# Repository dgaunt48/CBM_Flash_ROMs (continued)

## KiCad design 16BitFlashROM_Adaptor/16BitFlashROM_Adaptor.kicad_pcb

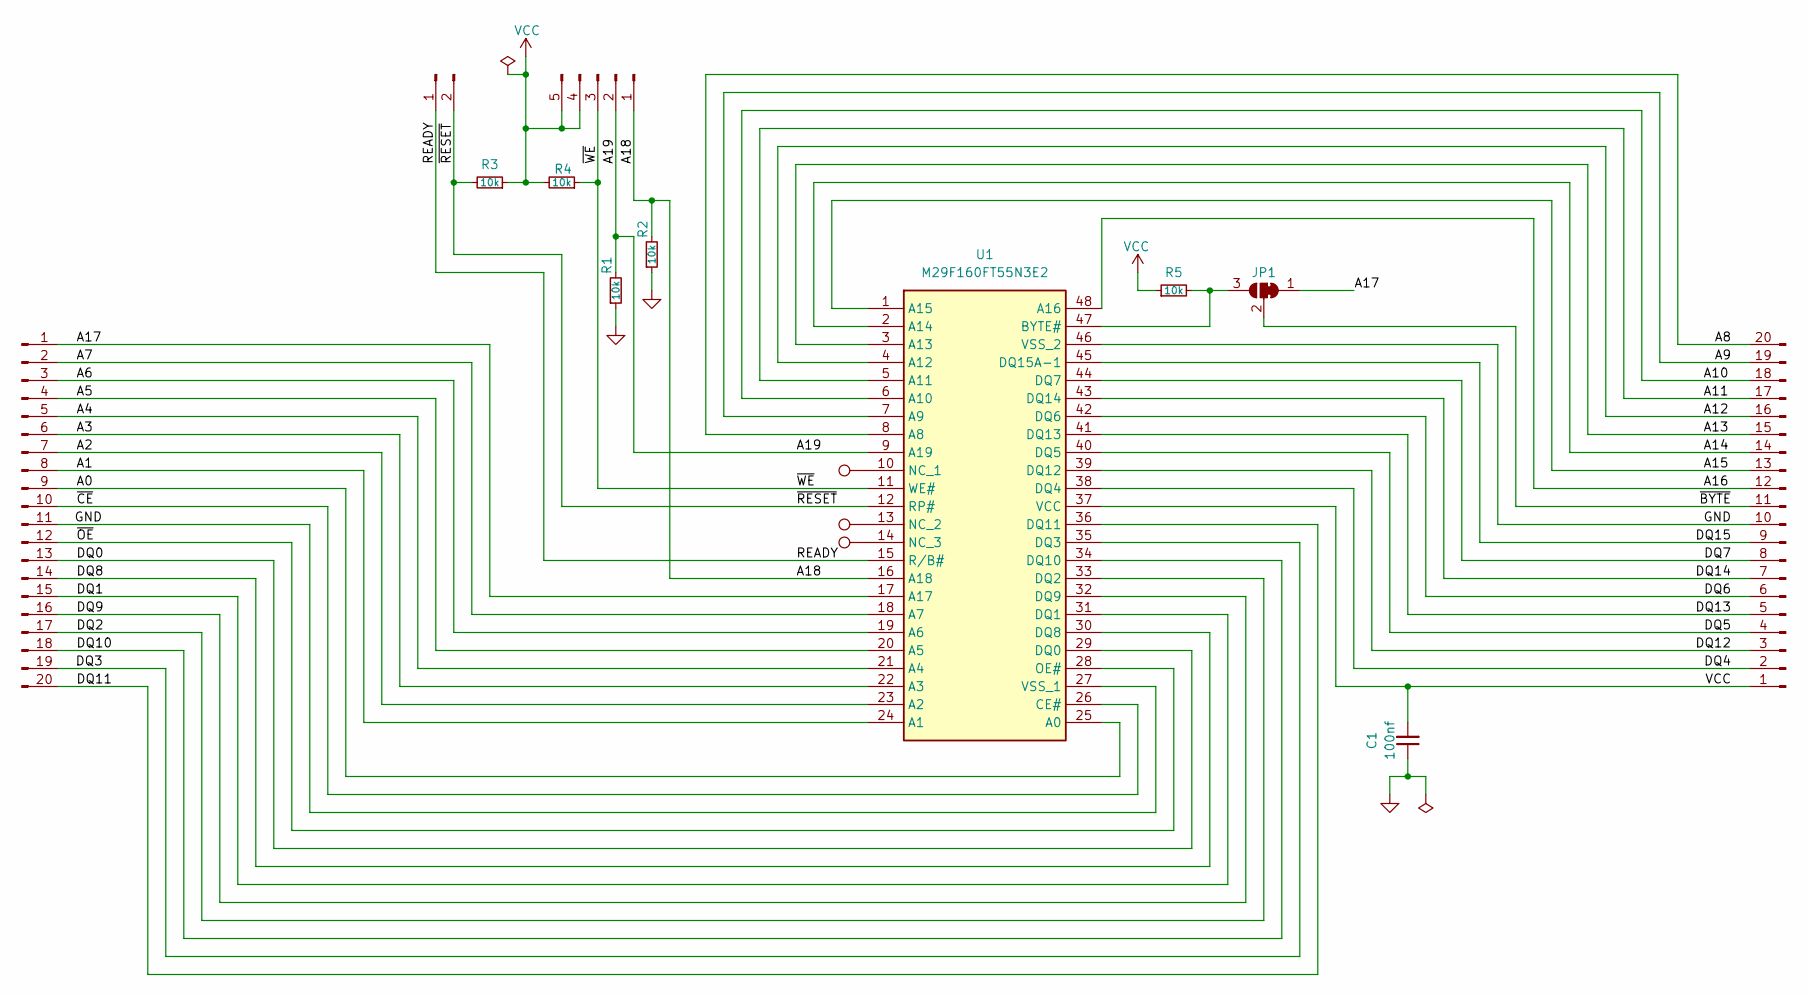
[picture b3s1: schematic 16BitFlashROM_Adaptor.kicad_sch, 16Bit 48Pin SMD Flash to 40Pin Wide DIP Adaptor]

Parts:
C1: 100nf; C_0603_1608Metric
J1: Address; PinHeader_Amiga_ROM
J2: Right Pins; PinHeader_1x20_P2.54mm_Vertical
J3: Reset; PinHeader_1x02_P2.54mm_Vertical
J5: Left Pins; PinHeader_1x20_P2.54mm_Vertical
JP1: SolderJumper_3_Bridged12; SolderJumper-3_P1.3mm_Bridged2Bar12_RoundedPad1.0x1.5mm
R1, R2, R3, R4, R5: 10k; R_0603_1608Metric
TP1, TP2, TP3: TestPoint; TestPoint_Pad_D1.0mm
U1: M29F160FT55N3E2; SOP50P2000X120-48N; Mouser Part Number 913-M29F160FT55N3E2

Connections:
/A0: J5.9, U1.25 (A0)
/A1: J5.8, U1.24 (A1)
/A2: J5.7, U1.23 (A2)
/A3: J5.6, U1.22 (A3)
/A4: J5.5, U1.21 (A4)
/A5: J5.4, U1.20 (A5)
/A6: J5.3, U1.19 (A6)
/A7: J5.2, U1.18 (A7)
/A8: J2.20, U1.8 (A8)
/A9: J2.19, U1.7 (A9)
/A10: J2.18, U1.6 (A10)
/A11: J2.17, U1.5 (A11)
/A12: J2.16, U1.4 (A12)
/A13: J2.15, U1.3 (A13)
/A14: J2.14, U1.2 (A14)
/A15: J2.13, U1.1 (A15)
/A16: J2.12, U1.48 (A16)
/A17: J5.1, JP1.1 (A), U1.17 (A17)
/A18: J1.1, R2.2, U1.16 (A18)
/A19: J1.2, R1.2, U1.9 (A19)
/DQ0: J5.13, U1.29 (DQ0)
/DQ1: J5.15, U1.31 (DQ1)
/DQ2: J5.17, U1.33 (DQ2)
/DQ3: J5.19, U1.35 (DQ3)
/DQ4: J2.2, U1.38 (DQ4)
/DQ5: J2.4, U1.40 (DQ5)
/DQ6: J2.6, U1.42 (DQ6)
/DQ7: J2.8, U1.44 (DQ7)
/DQ8: J5.14, U1.30 (DQ8)
/DQ9: J5.16, U1.32 (DQ9)
/DQ10: J5.18, U1.34 (DQ10)
/DQ11: J5.20, U1.36 (DQ11)
/DQ12: J2.3, U1.39 (DQ12)
/DQ13: J2.5, U1.41 (DQ13)
/DQ14: J2.7, U1.43 (DQ14)
/DQ15: J2.9, U1.45 (DQ15A-1)
/READY: J3.1, U1.15 (R/B#)
/~BYTE: J2.11, JP1.2 (C)
/~CE: J5.10, U1.26 (CE#)
/~OE: J5.12, U1.28 (OE#)
/~RESET: J3.2, R3.2, U1.12 (RP#)
/~WE: J1.3, R4.1, U1.11 (WE#)
GND: C1.1, J2.10, J5.11, R1.1, R2.1, U1.27 (VSS_1), U1.46 (VSS_2)
unnamed: JP1.3 (B), R5.2, U1.47 (BYTE#)
unnamed: TP1.1, U1.10 (NC_1)
unnamed: TP2.1, U1.13 (NC_2)
unnamed: TP3.1, U1.14 (NC_3)
VCC: C1.2, J1.4, J1.5, J2.1, R3.1, R4.2, R5.1, U1.37 (VCC)

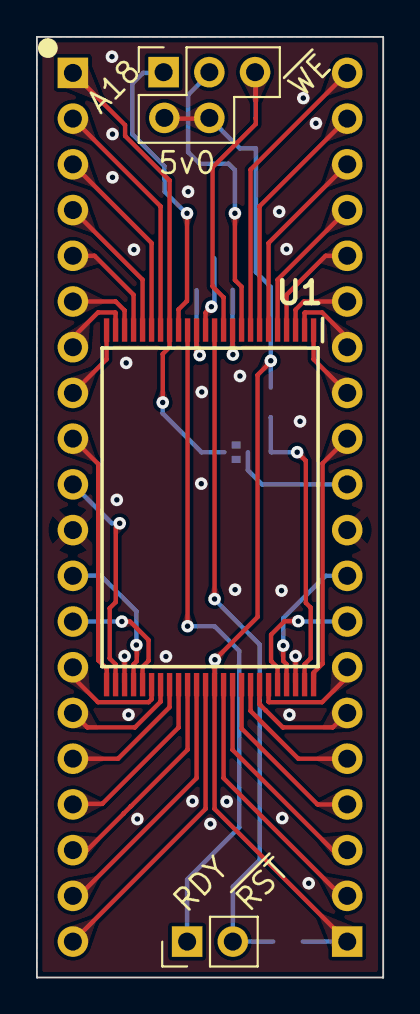
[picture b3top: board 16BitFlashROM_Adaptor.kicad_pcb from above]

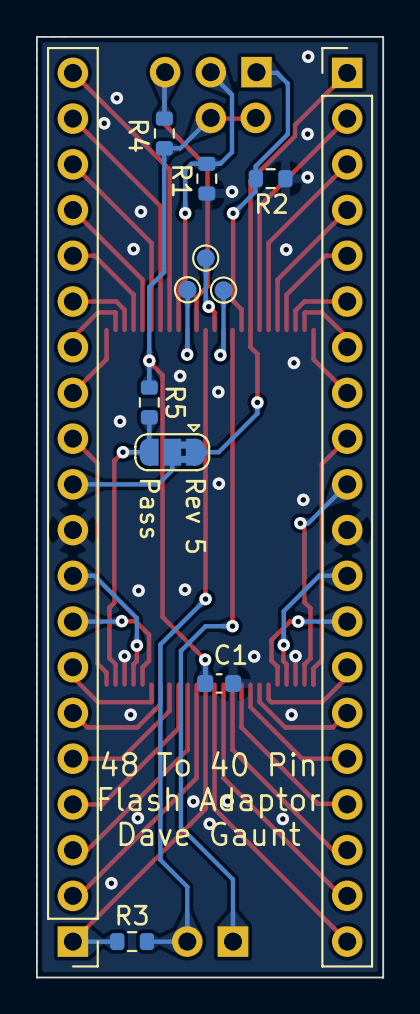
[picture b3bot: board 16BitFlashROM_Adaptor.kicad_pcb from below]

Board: 2 copper layers, 19.2 x 52.3 mm, 15 parts (12 on the bottom side), 48 nets.

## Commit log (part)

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2026-01-27 - Initial commit.
2026-01-28 - Added the 16bit 48pin SMD Flash to DIP40 adaptor board.
2026-01-28 - Updated Vic20 Flash Cart files to Ki-CAD 9.x - Cleaned up some component names and generated ibom's
2026-02-03 - Added the Flash Cartridge Programmer KiCad Project.
2026-02-13 - Add FatFS SD Card Library.
2026-02-13 - Added build to ignore.
2026-02-13 - Fixed A Couple Of Silk Screen Errors
2026-02-13 - Added VGA Output.
2026-02-13 - Was Getting Random Verify Read Errors From The Flash Rom, Need To Keep A Look Out But Seems To Be Fixed Now.
2026-02-14 - Added A Couple Of 5v Pins To Easily Jumper The Additional ROM Banks.
2026-02-15 - Generated New ibom For 16Bit Flash ROM Adaptor.
2026-03-01 - Cleanup a bit.
2026-03-02 - Read The Flash Manufacturers ID And Then Verified The ROM Image.
2026-03-02 - Cleaned up code quite a bit and added more manufacturer info.
2026-03-08 - Just read and verified an original kickstart 1.2 rom ic. - Added ASCII to PETSCII conversion to ROM dump display.
2026-03-08 - Added Flash ROM Detection For Macronix.
2026-03-08 - Split FlashInitialise Out Into A Seperate Function.
2026-03-09 - Added better support for switching between 8 and 16 bit flash roms. - Added display dump of Amiga 16 bit mask roms.
2026-03-09 - Successfully wrote and verified a 16 bit Amiga kickstart ROM image.
2026-03-14 - Added Flash Sector Erase.
2026-03-14 - Added the last bits and pieces from the old flash code.
2026-03-14 - Added support for some larger Micron Flash IC's - Fix a bug with the 16 bit single sector clear.
2026-04-02 - Modified to use my common folder so things stay up to date.
2026-04-26 - Updated ReadMe
2026-04-26 - Updated to KiCad 10.
2026-04-26 - Added the old FlashSPI project for writing an iCE40 BitStream to the FPGA's Flash ROM.
2026-05-02 - Changes to match the layout structure of my newer projects.
2026-06-03 - Updated to use pico SDK to 2.2
2026-06-20 - Updated To KiCad 10.0
2026-06-20 - Updated SDCard_WriteToFlash To Better Handle Files With Lots Of 0xFF's In Them
